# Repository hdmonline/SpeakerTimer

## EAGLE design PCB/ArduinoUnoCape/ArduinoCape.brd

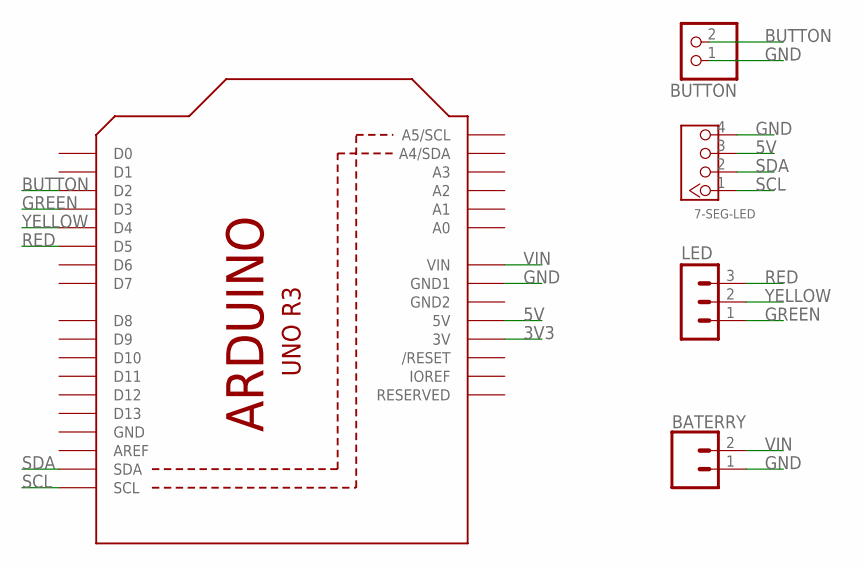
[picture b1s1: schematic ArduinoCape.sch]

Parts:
7-SEG-LED: GROVE-CONNECTOR-DIP(4P-2.0); HW4-2.0
BATERRY: CONN_02JST-PTH-2; JST-2-PTH
BUTTON: PINHD-1X2; 1X02
LED: MA03-1
U1: ARDUINOR3-DIMENSION; ARDUINOR3

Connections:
3V3: U1.3V
5V: 7-SEG-LED.3, U1.5V
BUTTON: BUTTON.2, U1.D2
GND: 7-SEG-LED.4, BATERRY.1, BUTTON.1, U1.GND, U1.GND1
GND2: U1.GND2
GREEN: LED.1, U1.D3
RED: LED.3, U1.D5
SCL: 7-SEG-LED.1, U1.SCL
SDA: 7-SEG-LED.2, U1.SDA
VIN: BATERRY.2, U1.VIN
YELLOW: LED.2, U1.D4

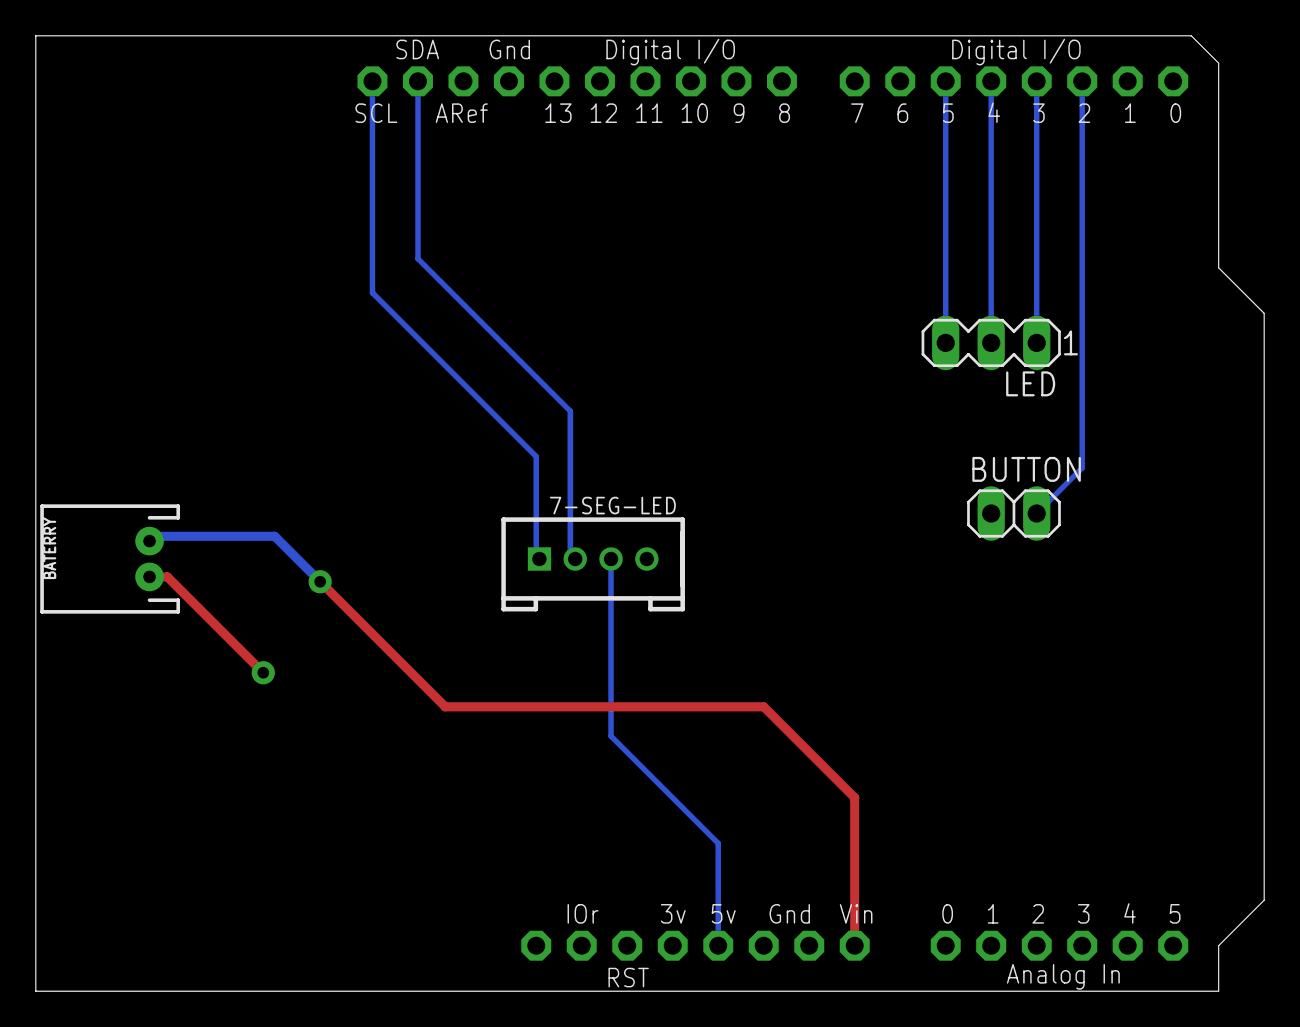
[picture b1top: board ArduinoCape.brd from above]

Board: 2 copper layers, 68.6 x 53.3 mm, 5 parts (0 on the bottom side), 9 nets.

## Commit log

2017-11-01 added arduino code
2017-11-02 update arduino code
    - added serLCD lib
    - added lcd code in SpeakerTime
    - added some documents about LCD
2017-11-03 added led code
2017-11-03 updated arduino code
2017-11-03 done arduino code
2017-11-03 added pcb
2017-11-05 updated pcb and code
2017-11-06 added cad model
2017-11-07 asdf
2017-11-17 updated model

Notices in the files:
parts and their libraries:
SparkFun-Connectors: Licensing: Creative Commons ShareAlike 4.0 International - https://creativecommons.org/licenses/by-sa/4.0
